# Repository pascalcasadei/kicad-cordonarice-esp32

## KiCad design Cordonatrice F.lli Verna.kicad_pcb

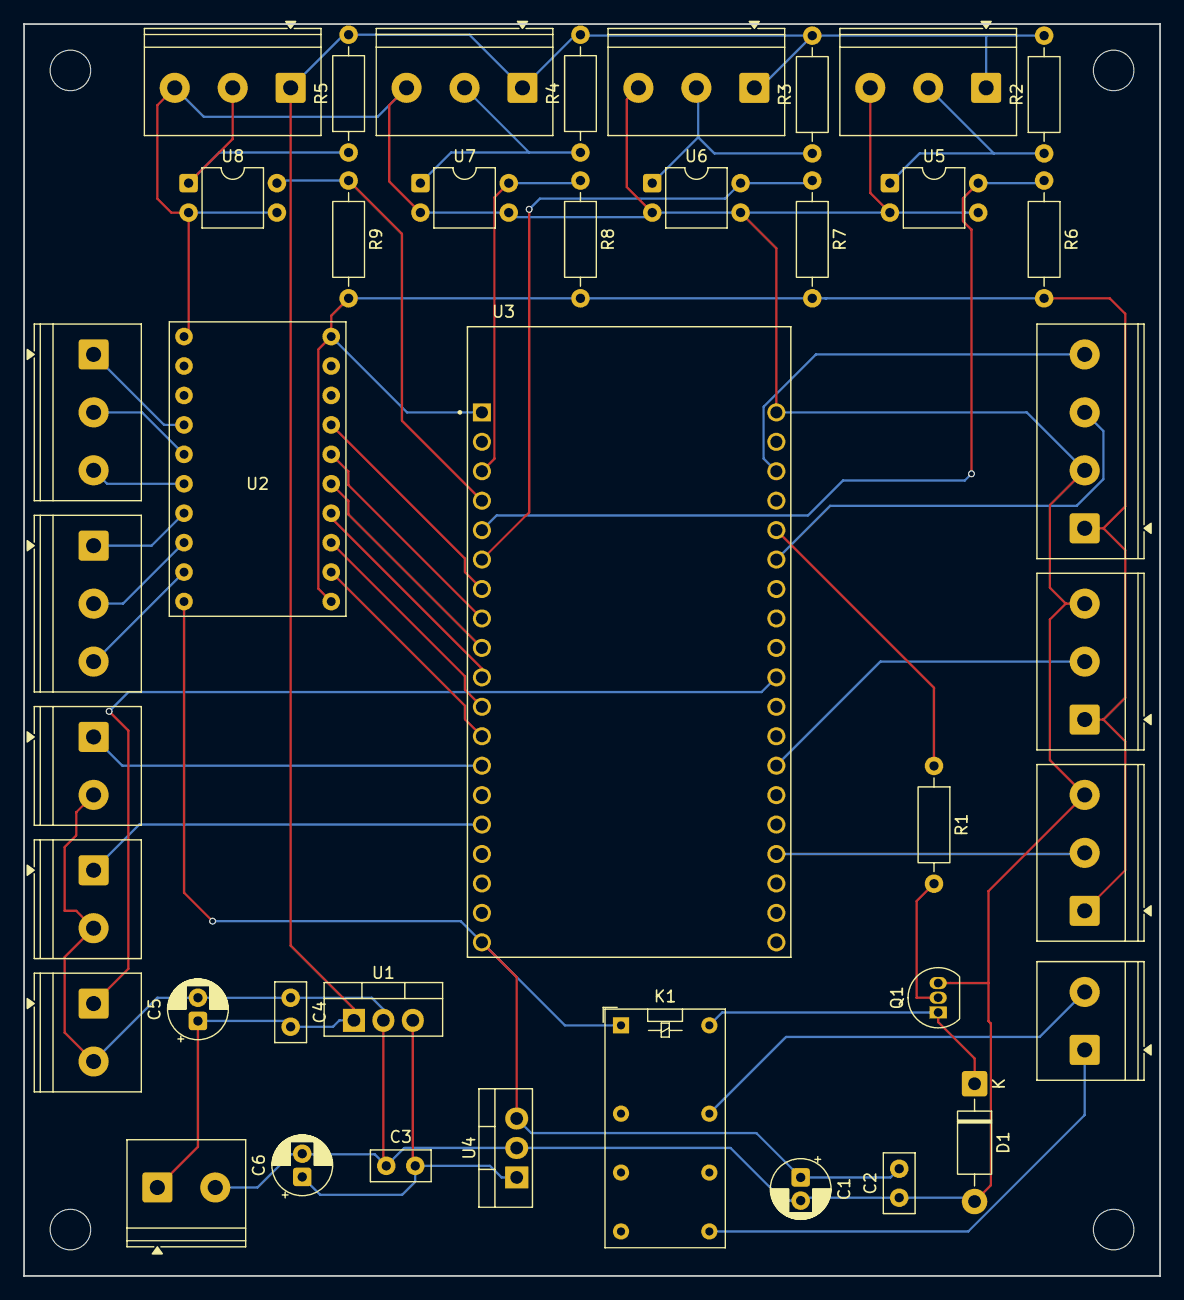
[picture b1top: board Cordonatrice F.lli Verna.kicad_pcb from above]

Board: 2 copper layers, 98.0 x 108.0 mm, 44 parts (0 on the bottom side), 37 nets.

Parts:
C1, C5, C6: 22uF_50V; CP_Radial_D5.0mm_P2.00mm
C2, C3, C4: 100nF_Ceramic; C_Disc_D5.0mm_W2.5mm_P2.50mm
D1: 1N4007; D_DO-41_SOD81_P10.16mm_Horizontal
ForoAltoDX: MountingHole_3.5mm
ForoAltoSX: MountingHole_3.5mm
ForoBassoDX: MountingHole_3.5mm
ForoBassoSX: MountingHole_3.5mm
J1, J2, J3, J4, J5, J6, J7, J8: Screw_Terminal_3_P5.00mm; TerminalBlock_Phoenix_PT-1,5-3-5.0-H_1x03_P5.00mm_Horizontal
J9, J10, J11, J13, J14: Screw_Terminal_2_P5.00mm; TerminalBlock_Phoenix_PT-1,5-2-5.0-H_1x02_P5.00mm_Horizontal
J12: Screw_Terminal_4_P5.00mm; TerminalBlock_Phoenix_PT-1,5-4-5.0-H_1x04_P5.00mm_Horizontal
K1: G5V-2; Relay_DPDT_Omron_G5V-2
Q1: BC548; TO-92_Inline
R1, R2, R3, R4, R5: 2.2k; R_Axial_DIN0207_L6.3mm_D2.5mm_P10.16mm_Horizontal
R6, R7, R8, R9: 10k; R_Axial_DIN0207_L6.3mm_D2.5mm_P10.16mm_Horizontal
U1: LM7812_TO220; TO-220-3_Vertical
U2: TX0108E-Breakout; txs0108e-breakout
U3: ESP32-DEVKITC-32D; MODULE_ESP32-DEVKITC-32D
U4: LM7805_TO220; TO-220-3_Vertical
U5, U6, U7, U8: PC817; DIP-4_W7.62mm

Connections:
+3.3V: J7.1, J8.1, J12.1, R6.2, R7.2, R8.2, R9.2, U2.0 (VA), U2.9 (OE), U3.J2-1 (3V3)
+5V: C1.1, C2.2, K1.1, U2.19 (VB), U3.J2-19 (EXT_5V), U4.3 (VO)
+24V: C4.2, C5.1, J1.1, J2.1, J3.1, J4.1, J13.1, R2.2, R3.2, R4.2, R5.2, U1.1 (VI)
BT_PAUSE: J11.1, U3.J3-10 (IO5)
BT_START: J9.1, U3.J2-13 (IO12)
BT_STOP: J10.1, U3.J2-15 (IO13)
DIR_PIN_X: J5.2, U2.17 (B2)
DIR_PIN_Y: J6.2, U2.14 (B5)
DIR_X_MIC.: U2.2 (A2), U3.J2-11 (IO27)
DIR_Y_MIC.: U2.5 (A5), U3.J2-8 (IO33)
ENABLE_PIN_X: J5.1, U2.16 (B3)
ENABLE_PIN_Y: J6.1, U2.13 (B6)
ENBL_X_MIC.: U2.3 (A3), U3.J2-10 (IO26)
ENBL_Y_MIC.: U2.6 (A6), U3.J2-7 (IO32)
GND: C1.2, C2.1, C3.1, C4.1, C5.2, C6.2, D1.2 (A), J1.3, J2.3, J3.3, J4.3, J7.3, J8.3, J9.2, J10.2, J11.2, J12.2, J13.2, Q1.3 (E), U1.2 (GND), U2.10 (GND), U3.J3-1 (GND3), U4.2 (GND), U5.2, U5.3, U6.2, U6.3, U7.2, U7.3, U8.2, U8.3
LIMIT_X_MAX: R7.1, U3.J2-6 (IO35), U6.4
LIMIT_X_MIN: R6.1, U3.J2-5 (IO34), U5.4
LIMIT_Y_MAX: R9.1, U3.J2-4 (SENSOR_VN), U8.4
LIMIT_Y_MIN: R8.1, U3.J2-3 (SENSOR_VP), U7.4
unnamed: D1.1 (K), K1.16, Q1.1 (C)
unnamed: J1.2, R2.1, U5.1
unnamed: J2.2, R3.1, U6.1
unnamed: J3.2, R4.1, U7.1
unnamed: J4.2, R5.1, U8.1
unnamed: J14.1, K1.9
unnamed: J14.2, K1.13
unnamed: Q1.2 (B), R1.2
unnamed: C3.2, C6.1, U1.3 (VO), U4.1 (VI)
POT_M1: J7.2, U3.J3-16 (IO15)
POT_M2: J8.2, U3.J3-13 (IO4)
SCL: J12.4, U3.J3-3 (IO22)
SDA: J12.3, U3.J3-6 (IO21)
STEP_PIN_X: J5.3, U2.18 (B1)
STEP_PIN_Y: J6.3, U2.15 (B4)
STEP_X_MIC.: U2.1 (A1), U3.J2-12 (IO14)
STEP_Y_MIC.: U2.4 (A4), U3.J2-9 (IO25)
rele_fiaccola: R1.1, U3.J3-5 (RXD0)

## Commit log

2025-09-27 added all modified files
2025-09-27 sostituzione esp32
2025-09-27 correzione schema corretto
2025-09-28 aggiunta 7824
2025-09-28 aggiunta diodo su transistor
2025-09-30 applicato freerouting
2025-09-30 secondo aggiornamento piste
